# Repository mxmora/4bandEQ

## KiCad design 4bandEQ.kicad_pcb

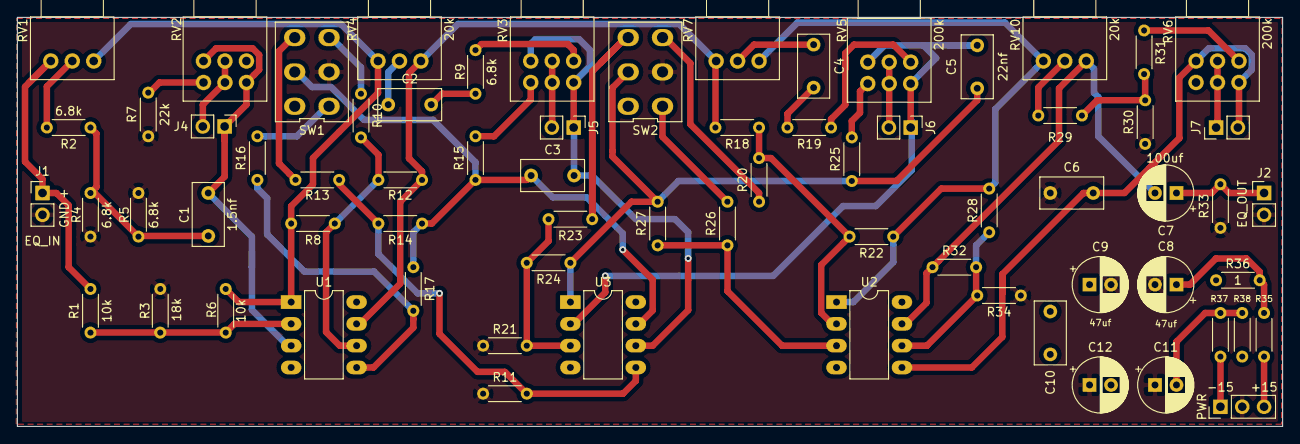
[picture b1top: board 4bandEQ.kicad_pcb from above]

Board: 2 copper layers, 147.3 x 47.6 mm, 70 parts (0 on the bottom side), 51 nets.

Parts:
C1, C2, C3: 1.5nf; C_Rect_L7.2mm_W3.5mm_P5.00mm_FKS2_FKP2_MKS2_MKP2
C4, C5: 22nf; C_Rect_L7.2mm_W3.5mm_P5.00mm_FKS2_FKP2_MKS2_MKP2
C6: 6.8nf; C_Rect_L7.2mm_W3.5mm_P5.00mm_FKS2_FKP2_MKS2_MKP2
C7: 100uf; CP_Radial_D6.3mm_P2.50mm
C8, C9, C11, C12: 47uf; CP_Radial_D6.3mm_P2.50mm
C10: 40nf; C_Rect_L7.2mm_W3.5mm_P5.00mm_FKS2_FKP2_MKS2_MKP2
J1: EQ_IN; PinHeader_1x02_P2.54mm_Vertical
J2: EQ_OUT; PinHeader_1x02_P2.54mm_Vertical
J3: PWR; PinHeader_1x03_P2.54mm_Vertical
J4: H_JMP; PinHeader_1x02_P2.54mm_Vertical
J5: MF1_JMP; PinHeader_1x02_P2.54mm_Vertical
J6: MF2_JMP; PinHeader_1x02_P2.54mm_Vertical
J7: LF_JMP; PinHeader_1x02_P2.54mm_Vertical
R1, R6, R8, R12, R17, R18, R22, R27, R28, R32: 10k; R_Axial_DIN0204_L3.6mm_D1.6mm_P5.08mm_Horizontal
R2, R4, R5, R9, R11, R14, R15, R16, R19, R21, R24, R25, R26: 6.8k; R_Axial_DIN0204_L3.6mm_D1.6mm_P5.08mm_Horizontal
R3: 18k; R_Axial_DIN0204_L3.6mm_D1.6mm_P5.08mm_Horizontal
R7, R31: 22k; R_Axial_DIN0204_L3.6mm_D1.6mm_P5.08mm_Horizontal
R10, R20: 47k; R_Axial_DIN0204_L3.6mm_D1.6mm_P5.08mm_Horizontal
R13, R23: 12k; R_Axial_DIN0204_L3.6mm_D1.6mm_P5.08mm_Horizontal
R29: 15k; R_Axial_DIN0204_L3.6mm_D1.6mm_P5.08mm_Horizontal
R30: 8.2k; R_Axial_DIN0204_L3.6mm_D1.6mm_P5.08mm_Horizontal
R33: 100k; R_Axial_DIN0204_L3.6mm_D1.6mm_P5.08mm_Horizontal
R34: 27k; R_Axial_DIN0204_L3.6mm_D1.6mm_P5.08mm_Horizontal
R35, R36, R37, R38: 1; R_Axial_DIN0204_L3.6mm_D1.6mm_P5.08mm_Horizontal
RV1, RV4, RV7, RV10: 20k; Potentiometer_Alps_RK097_Single_Horizontal
RV2, RV3, RV5, RV6: 200k; Potentiometer_Alps_RK097_Dual_Horizontal
SW1: MF1_IN; PB_SW_F2UEE
SW2: MF2_IN; PB_SW_F2UEE
U1, U2, U3: TL072; DIP-8_W7.62mm_LongPads

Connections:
+15V: J3.3, R35.2
+VC: C9.1, C10.1, R36.1, U1.8, U2.8, U3.8
-15V: J3.1, R37.2
-VC: C10.2, C12.2, R38.1, U1.4, U2.4, U3.4
GND: C6.1, C8.2, C9.2, C11.1, C12.1, J1.2, J2.2, J3.2, R3.1, R4.1, R5.1, R7.1, R11.1, R21.1, R30.1, R33.1, R34.1, SW1.2, SW2.2
unnamed: C1.1, J4.1, RV2.3, RV2.4, U1.3
unnamed: C1.2, R2.1, R4.2, R5.2
unnamed: C2.1, RV4.2
unnamed: C2.2, R9.2
unnamed: C3.1, R14.1, R15.1, R17.1, SW1.5, U3.7
unnamed: C3.2, J5.1, RV3.3, RV3.4, U3.6
unnamed: C4.1, RV7.2
unnamed: C4.2, R19.2
unnamed: C5.1, R24.1, R25.1, R27.1, SW2.5, U3.1
unnamed: C5.2, J6.1, RV5.3, RV5.4, U3.2
unnamed: C6.2, J7.2, RV6.3, RV6.4, U2.5
unnamed: C7.1, J2.1, R33.2
unnamed: C7.2, R32.1, RV10.1, U2.7
unnamed: C8.1, R35.1, R36.2
unnamed: C11.2, R37.1, R38.2
unnamed: J1.1, R1.2, RV1.3
unnamed: J4.2, RV2.2, RV2.5
unnamed: J5.2, RV3.2, RV3.5
unnamed: J6.2, RV5.2, RV5.5
unnamed: J7.1, RV6.2, RV6.5
unnamed: R1.1, R3.2, R6.2, U1.2
unnamed: R2.2, RV1.2
unnamed: R6.1, R8.2, RV1.1, RV4.3, U1.1
unnamed: R7.2, RV2.6
unnamed: R9.1, RV3.1
unnamed: R10.1, SW1.3
unnamed: R8.1, R10.2, R12.2, U1.6
unnamed: R11.2, R13.2, R14.2, U3.5
unnamed: R12.1, R18.2, RV4.1, RV7.3, U1.7
unnamed: R13.1, SW1.4
unnamed: R15.2, RV3.6
unnamed: R16.1, R17.2, U1.5
unnamed: R16.2, SW1.1
unnamed: R18.1, R20.2, R22.2, U2.2
unnamed: R19.1, RV5.1
unnamed: R20.1, SW2.3
unnamed: R21.2, R23.2, R24.2, U3.3
unnamed: R22.1, R28.2, RV7.1, RV10.3, U2.1
unnamed: R23.1, SW2.4
unnamed: R25.2, RV5.6
unnamed: R26.1, R27.2, U2.3
unnamed: R26.2, SW2.1
unnamed: R28.1, R32.2, R34.2, U2.6
unnamed: R29.1, R30.2, R31.2
unnamed: R29.2, RV10.2
unnamed: R31.1, RV6.1

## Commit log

2019-11-20 first check in
2019-11-22 start layout
2019-12-06 layout board
